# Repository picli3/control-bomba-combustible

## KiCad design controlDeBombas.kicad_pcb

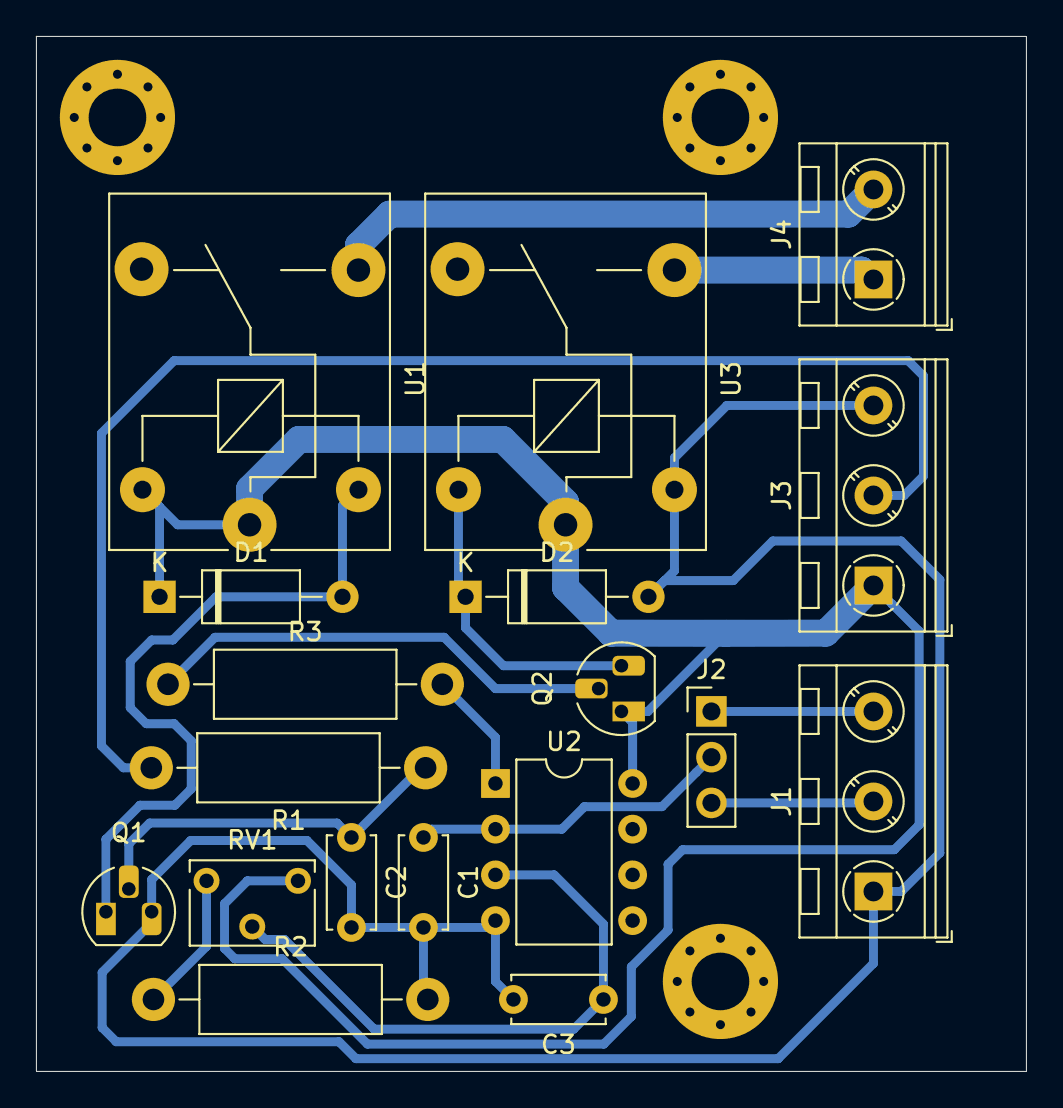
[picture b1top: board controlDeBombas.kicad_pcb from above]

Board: 2 copper layers, 55.0 x 57.5 mm, 18 parts (0 on the bottom side), 15 nets.

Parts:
C1, C2, C3: 100nF; C_Disc_D5.0mm_W2.5mm_P5.00mm
D1: D_ALT; D_A-405_P10.16mm_Horizontal
D2: 1N4007; D_A-405_P10.16mm_Horizontal
J1: SENSE; TerminalBlock_RND_205-00046_1x03_P5.00mm_Horizontal
J2: SELECT; PinHeader_1x03_P2.54mm_Vertical
J3: INPUT; TerminalBlock_RND_205-00046_1x03_P5.00mm_Horizontal
J4: OUTPUTS; TerminalBlock_RND_205-00045_1x02_P5.00mm_Horizontal
Q1, Q2: 2N3904; TO-92_HandSolder
R1, R3: 10K; R_Axial_DIN0411_L9.9mm_D3.6mm_P15.24mm_Horizontal
R2: 100; R_Axial_DIN0411_L9.9mm_D3.6mm_P15.24mm_Horizontal
RV1: 5K; Potentiometer_Bourns_3266W_Vertical
U1, U3: SRD-12VDC; Relay_SPDT_SANYOU_SRD_Series_Form_C
U2: TL082; DIP-8_W7.62mm

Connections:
+12V: D1.1 (K), J3.1, Q2.1 (C), RV1.1, U1.1 (CO), U1.5 (+), U2.8 (vcc), U3.1 (CO)
/OUT_1: J4.2, U1.3 (C)
/OUT_2: J4.1, U3.3 (C)
/SENSE: C1.1, J2.2, U2.2 (-)
GND: C1.2, C2.2, C3.2, D2.2 (A), J1.1, J3.3, Q1.3 (E), R2.2, U2.4, U3.2 (-)
unnamed: C2.1, Q1.2 (B), R1.1
unnamed: C3.1, RV1.2, U2.3 (+)
unnamed: D1.2 (A), Q1.1 (C), U1.2 (-)
unnamed: D2.1 (K), Q2.3 (E), U3.5 (+)
unnamed: J1.2, J2.3
unnamed: J1.3, J2.1
unnamed: J3.2, R1.2
unnamed: Q2.2 (B), R3.1
unnamed: R2.1, RV1.3
unnamed: R3.2, U2.1

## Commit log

2022-06-12 prodcuto final
